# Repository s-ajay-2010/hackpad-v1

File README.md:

# HackPad V-1

This is my first hardware project where I've made a mini keyboard with 3 switches which can control the music playing like ```skip to next```, ```play previous track```, ```play/pause track``` and rotary switch for ```increasing and decreasing volume``` and ```mute and unmute```.

## Stack:
- QMK for firmware
- XIAO-RP2040 for the main processor
- MX-Style mechanical swtiches for keys
- EC11E Rotary Encoder(with swtich) for the rotary switch

## Demo files

for the actual 3-d model's STEP files, check [here](CAD/)
## Instalation guide
Check [qmk's guide](https://qmk.fm/guide) for firmware flashing.
For firmware folder check [here](hackpad-v1_firmware)

And as for the pcb part just open it on kicad and edit it or you can just export the gerber files and print them out.

## BOM
|Name                               |Quantity|Total Cost                         |Distributor      |
|-----------------------------------|--------|-----------------------------------|-----------------|
|PCB                                |1       |9.86 USD                           |JLCPCB           |
|MX-Style swtiches                  |3       |0(provided with hackpad kit)       |HackClub         |
|EC11E Rotary Encoder(with swtich)  |1       |0(provided with hackpad kit)       |HackClub         |
|                                   | Total  |9 USD                              |                 |

##

That's all, enjoy your hackpad yayayay

## AI Usage
I wrote my firmware with a lilte bit help of AI, like just for understanding C-language

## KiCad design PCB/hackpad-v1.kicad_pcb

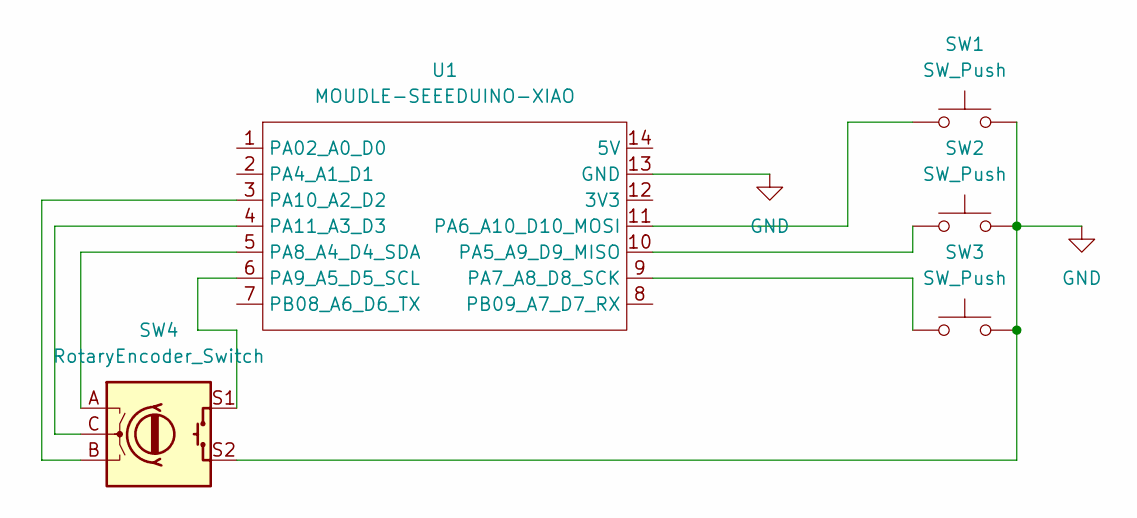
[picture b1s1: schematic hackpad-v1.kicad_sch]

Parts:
SW1, SW2, SW3: SW_Push; SW_Cherry_MX_1.00u_PCB
SW4: RotaryEncoder_Switch; RotaryEncoder_Alps_EC11E-Switch_Vertical_H20mm
U1: MOUDLE-SEEEDUINO-XIAO; XIAO-Generic-Hybrid-14P-2.54-21X17.8MM

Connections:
GND: SW1.2, SW2.2, SW3.2, SW4.S2, U1.13 (GND)
unnamed: SW2.1, U1.10 (PA5_A9_D9_MISO)
unnamed: SW1.1, U1.11 (PA6_A10_D10_MOSI)
unnamed: SW3.1, U1.9 (PA7_A8_D8_SCK)
unnamed: SW4.A, U1.5 (PA8_A4_D4_SDA)
unnamed: SW4.S1, U1.6 (PA9_A5_D5_SCL)
unnamed: SW4.B, U1.3 (PA10_A2_D2)
unnamed: SW4.C, U1.4 (PA11_A3_D3)

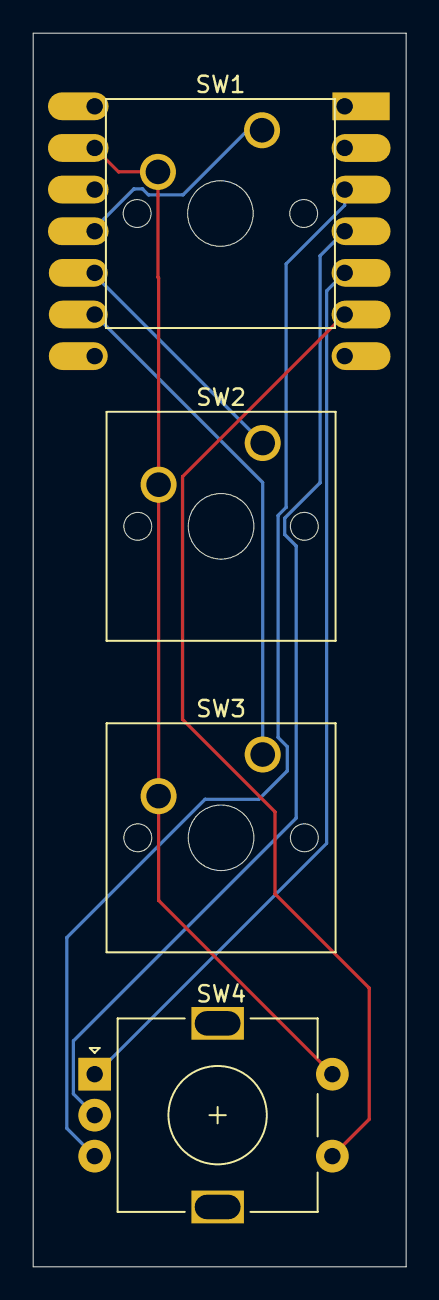
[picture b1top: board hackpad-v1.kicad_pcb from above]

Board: 2 copper layers, 22.8 x 75.2 mm, 5 parts (1 on the bottom side), 8 nets.

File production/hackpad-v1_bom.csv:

"Id";"Designator";"Footprint";"Quantity";"Designation";"Supplier and ref";
1;"SW1, SW2, SW3";"SW_Cherry_MX_1.00u_PCB";3;"SW_Push";;;
2;"SW4";"RotaryEncoder_Alps_EC11E-Switch_Vertical_H20mm";1;"RotaryEncoder_Switch";;;
3;"U1";"XIAO-Generic-Hybrid-14P-2.54-21X17.8MM";1;"MOUDLE-SEEEDUINO-XIAO";;;
